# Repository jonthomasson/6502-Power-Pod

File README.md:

# 6502-Power-Pod
6502-Power-Pod

This is a very simple power supply I built using linear regulators for a few projects a year or two ago. I've used it a number of times since, and it's proved to be very stable and reliable at delivering 5v and 3.3v. The supply provides an on/off switch and has a barrel jack that accepts between 7-12v dc.

![enter image description here](https://lh3.googleusercontent.com/YYRoUtu9Ivtf3oqEvA_Q3FOaGBNRtuT4A_om7Lkq5QirhgERYamO0zOTS7jfc7dau_pBRYD3IEYtYgrGtr401ybBZzL9tx5nqnWwJd3ZAVfp4HEolbSqTfV2LOycUkd97ZvmKxcsnh6EOxqqPigjNDPizSS57IFicbzUFKmWCKB_JswyAneYQ0L_6hUoyZVcJYSx-cJlpbUyTF77w-YuQ1QWVhx2DBqwgSkhvTgzP0eOhVND3W6YmBLS5KzIemWJ7N54YVqj8VN0csuKCoWfofP-GOGnkh_qrtFvrkMnpybrKWinUj-w9iUD8qvzEgDs5bkGV4ZYsH4Ek1GgMBeIxuAFyWj_VBf5DjgO7IEfM601-33izL9ms91FOdOFazGIxnNpasHYczS-k0Vvs0mOwVRnrtVNNmeXeqPdaCSh_YMRAGkgAQn0T_mRiB6sUNYvBgC-YjVRfr_S-2FwaVbW1x-zksut--_6mRKK8_a5M7iLXj6mLNN4Xp99krIKcheGdLDnUMoAD6LpieU1ejb7OivoerwD_IOVC2u5bBrUdJs4NBBOR9cyhUdVAR84GcSCUVx4gCSPejFCoZQE7VNemK0_3PloTHsP71XkOLwz2Wc9O6zaCJWEcr0SgXMWDA2l5OfNjZ1GFpgYBJmQ1Bwg5YNhdPcJRwrF1w=w1184-h888-no)

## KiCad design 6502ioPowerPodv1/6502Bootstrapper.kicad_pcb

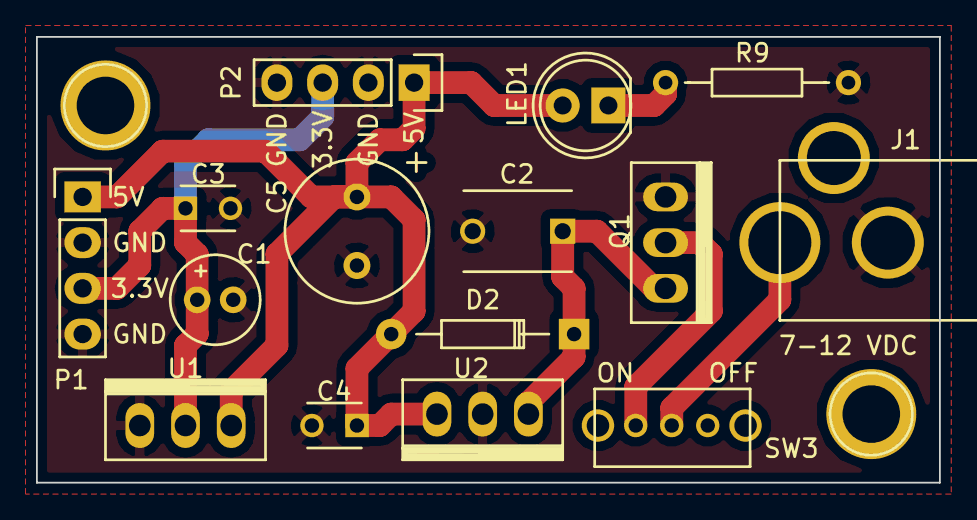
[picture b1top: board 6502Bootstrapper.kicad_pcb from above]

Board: 2 copper layers, 50.2 x 24.8 mm, 15 parts (0 on the bottom side), 7 nets.

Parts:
C1: 10uf; Elko_vert_11x5mm_RM2
C2: .33uf; C_Disc_D6_P5
C3, C4: .1uf; C_Disc_D3_P2.5
C5: 1000uf; Elko_vert_11.5x8mm_RM3.5
D2: D; Diode_DO-35_SOD27_Horizontal_RM10
J1: BARREL_JACK; Barrel_Jack_PJ002A
LED1: LED; LED-5MM
P1, P2: CONN_01X04; Pin_Header_Straight_1x04
Q1: P_MOSFET FQP47P06; FQP47P06_P_Mosfet
R9: 330; Resistor_Horizontal_RM10mm
SW3: SPST; SS_12D07_SWITCH
U1: LD1117V33; FQP47P06_P_Mosfet
U2: LM7805CV; FQP47P06_P_Mosfet

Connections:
+3V3: C1.1, C3.1, P1.3, P2.3, U1.2
+5V: C4.1, C5.1, D2.2, LED1.2, P1.1, P2.1, U1.3, U2.3
GND: C1.2, C2.2, C3.2, C4.2, C5.2, J1.2, P1.2, P1.4, P2.2, P2.4, Q1.1, R9.2, U1.1, U2.2
unnamed: C2.1, D2.1, Q1.3, U2.1
unnamed: J1.1, SW3.1
unnamed: LED1.1, R9.1
unnamed: Q1.2, SW3.2

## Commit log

2015-11-07 :space_invader: Added .gitattributes & .gitignore files
2015-11-07 initial checkin
